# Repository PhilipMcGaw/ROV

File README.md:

# ROV

This is the software that runs my ROV (well an attempt at writing it anyway).\

uses RPi-Cam-Web-Interface

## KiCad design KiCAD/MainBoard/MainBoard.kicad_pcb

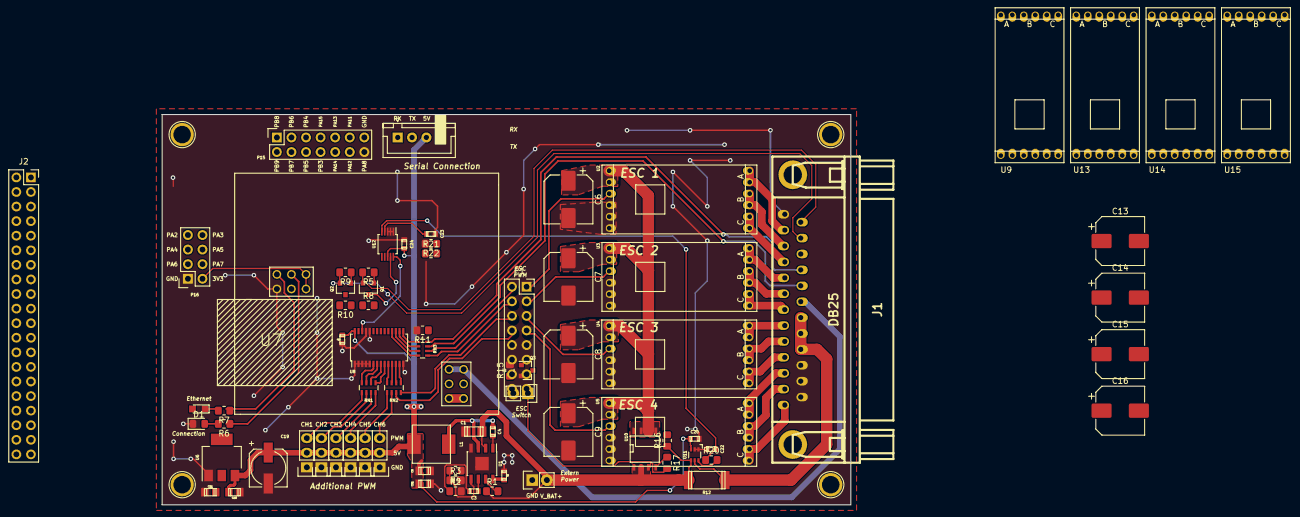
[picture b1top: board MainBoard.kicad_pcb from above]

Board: 2 copper layers, 120.0 x 68.0 mm, 82 parts (0 on the bottom side), 71 nets.

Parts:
C1: 10uF/25V; c_1206
C2, C20, C23, C24: 0.1uF; c_0603
C3: 3.9nF; c_0603
C4: 10nF; c_0603
C5, C21: 22uF/10V; c_0805
C6, C7, C8, C9, C13, C14, C15, C16: 220uF/25V; CP_Elec_8x10
C10, C11: 1uF; c_0805
C12: 10uF; c_0603
C19: 220uF/10V; CP_Elec_6.3x5.8
C22: 1uF; c_0603
D1: LED; LED_0805_2012Metric_Pad1.15x1.40mm_HandSolder
D2: LED; LED_0805
J1: DB25; DB_25M
J2: Raspberry_Pi_2_3; PinSocket_2x20_P2.54mm_Vertical
L1: 10uH/4A; ASPI-0630LR
P1: BDLC Enable; PinSocket_2x08_P2.54mm_Vertical
P2: CONN_01X04; JST_XH_B04B-XH-A_04x2.50mm_Straight
P4, P5, P6, P7: HOLE; 1pin
P8, P14: CONN_01X02; Socket_Strip_Straight_1x02
P9, P10, P11, P12, P13, P18: CONN_01X03; Socket_Strip_Straight_1x03
P15: CONN_02X07; Socket_Strip_Straight_2x07
P16: CONN_02X04; Socket_Strip_Straight_2x04
Q1, Q2: BSS138; SOT-23
Q3: DMN65D8L; SOT-23
R1: 100k; R_0805_2012Metric_Pad1.20x1.40mm_HandSolder
R2: 6.8k; R_0805_2012Metric_Pad1.20x1.40mm_HandSolder
R3, R22: 10k %1; R_0805_2012Metric_Pad1.20x1.40mm_HandSolder
R4: 44.2k 1%; R_0805_2012Metric_Pad1.20x1.40mm_HandSolder
R5, R8, R9, R10, R11, R15, R16: 10k; R_0805_2012Metric_Pad1.20x1.40mm_HandSolder
R6, R7: 330; R_0805_2012Metric_Pad1.20x1.40mm_HandSolder
R12: 0.003 %1; r_2512
R17: 1k; R_0805_2012Metric_Pad1.20x1.40mm_HandSolder
R20: 3.3k; R_0805_2012Metric_Pad1.20x1.40mm_HandSolder
R21: 30.1k 1%; R_0805_2012Metric_Pad1.20x1.40mm_HandSolder
RN1, RN2, RN3: 20k; R_Array_Concave_4x0603
U1: mp2307; SOIC-8-1EP_3.9x4.9mm_Pitch1.27mm
U2, U3, U4, U5, U9, U13, U14, U15: DYS_mini_ESC; DYS_Mini_ESC
U6: TLV1117LV33; SOT-223
U7: TENDA_P200; Tenda_p200
U8: pca9685; TSSOP-28_4.4x9.7mm_Pitch0.65mm
U10: SI4425DDY; SOIC-8-N
U11: INA199A2; SC-70-6
U12: ADS1015; MSOP-10_3x3mm_Pitch0.5mm

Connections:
+3V3: C11.1, D2.2 (A), J1.23, P16.2, Q1.1 (G), Q2.1 (G), R5.1, R9.1, U6.2 (VOUT), U6.4 (VOUT), U7.3V3
+5V: C5.1, C10.1, C12.1, C19.1, C20.1, C21.1, C24.1, J2.2 (5V), J2.4 (5V), L1.2, P2.3, P9.2, P10.2, P11.2, P12.2, P13.2, P18.2, R4.1, R8.1, R10.1, U6.3 (VIN), U8.28 (VDD), U11.3 (V+), U12.8 (VDD)
/ADC_I: C22.1, R20.1, U12.5 (AIN_1)
/ADC_V: C23.1, R21.2, R22.1, U12.4 (AIN_0)
/Brushless DC Controllers/ESC1: P1.1, U2.2 (PWM)
/Brushless DC Controllers/ESC2: P1.3, U3.2 (PWM)
/Brushless DC Controllers/ESC3: P1.5, U4.2 (PWM)
/Brushless DC Controllers/ESC4: P1.7, U5.2 (PWM)
/Brushless DC Controllers/ESC5: P1.9, U9.2 (PWM)
/Brushless DC Controllers/ESC6: P1.11, U13.2 (PWM)
/Brushless DC Controllers/ESC7: P1.13, U14.2 (PWM)
/Brushless DC Controllers/ESC8: P1.15, U15.2 (PWM)
/CH0: P9.3, RN1.1 (R1.1)
/CH1: P10.3, RN1.2 (R2.1)
/CH2: P11.3, RN1.3 (R3.1)
/CH3: P12.3, RN1.4 (R4.1)
/CH4: P13.3, RN2.1 (R1.1)
/CH5: P18.3, RN2.2 (R2.1)
/CH8: P1.2, RN3.8 (R1.2)
/CH9: P1.4, RN3.7 (R2.2)
/CH10: P1.6, RN3.6 (R3.2)
/CH11: P1.8, RN3.5 (R4.2)
/MOTOR_1A: J1.12, U2.4 (OUT_A)
/MOTOR_1B: J1.11, U2.5 (OUT_B)
/MOTOR_1C: J1.10, U2.6 (OUT_C)
/MOTOR_2A: J1.9, U3.4 (OUT_A)
/MOTOR_2B: J1.8, U3.5 (OUT_B)
/MOTOR_2C: J1.7, U3.6 (OUT_C)
/MOTOR_3A: J1.6, U4.4 (OUT_A)
/MOTOR_3B: J1.5, U4.5 (OUT_B)
/MOTOR_3C: J1.4, U4.6 (OUT_C)
/MOTOR_4A: J1.3, U5.4 (OUT_A)
/MOTOR_4B: J1.2, U5.5 (OUT_B)
/MOTOR_4C: J1.1, U5.6 (OUT_C)
/PWR_SW: Q3.1 (G), R15.1
/SCL_3V3: J1.24, J2.5 (SCL/GPIO3), Q2.2 (S), R9.2
/SCL_5V: Q2.3 (D), R10.2, U8.26 (SCL), U12.10 (SCL)
/SDA_3V3: J1.25, J2.3 (SDA/GPIO2), Q1.2 (S), R5.2
/SDA_5V: Q1.3 (D), R8.2, U8.27 (SDA), U12.9 (SDA)
/T+: J1.20, U7.T_+ (Tether+)
/V_BAT: C1.1, P8.2, R1.1, R12.1, R16.1, R21.1, U1.2 (IN), U10.1 (S), U10.2 (S), U10.3 (S), U11.4 (IN+)
/V_IN: J1.17, J1.18, J1.19, R12.2, U11.5 (IN-)
GND: C1.2, C2.2, C5.2, C6.2, C7.2, C8.2, C9.2, C10.2, C11.2, C12.2, C13.2, C14.2, C15.2, C16.2, C19.2, C20.2, C21.2, C22.2, C23.2, C24.2, D1.1 (K), J1.13, J1.14, J1.15, J1.16, J2.6 (GND), J2.9 (GND), J2.14 (GND), J2.20 (GND), J2.25 (GND), J2.30 (GND), J2.34 (GND), J2.39 (GND), P2.4, P8.1, P9.1, P10.1, P11.1, P12.1, P13.1, P14.2, P15.14, P16.1, P18.1, Q3.2 (S), R2.2, R3.2, R11.2, R15.2, R22.2, U1.4 (GND), U1.9 (GND), U2.1 (GND), U3.1 (GND), U4.1 (GND), U5.1 (GND), U6.1 (GND), U7.GND, U8.1 (A0), U8.2 (A1), U8.3 (A2), U8.4 (A3), U8.5 (A4), U8.14 (GND), U8.24 (A5), U8.25 (EXTCLK), U9.1 (GND), U11.1 (REF), U11.2 (GND), U12.1 (ADDR), U12.2 (ALERT), U12.3 (GND), U13.1 (GND), U14.1 (GND), U15.1 (GND)
unnamed: C3.2, R2.1
unnamed: D1.2 (A), R6.2
unnamed: D2.1 (K), R7.2
unnamed: P14.1, Q3.3 (D), R17.2
unnamed: RN1.8 (R1.2), U8.6 (PWM0)
unnamed: RN1.7 (R2.2), U8.7 (PWM1)
unnamed: RN1.6 (R3.2), U8.8 (PWM2)
unnamed: RN1.5 (R4.2), U8.9 (PWM3)
unnamed: RN2.8 (R1.2), U8.10 (PWM4)
unnamed: RN2.7 (R2.2), U8.11 (PWM5)
unnamed: RN2.6 (R3.2), U8.12 (PWM6)
unnamed: RN2.5 (R4.2), U8.13 (PWM7)
unnamed: RN3.1 (R1.1), U8.15 (PWM8)
unnamed: RN3.2 (R2.1), U8.16 (PWM9)
unnamed: RN3.3 (R3.1), U8.17 (PWM10)
unnamed: RN3.4 (R4.1), U8.18 (PWM11)
unnamed: C4.2, U1.1 (BS)
unnamed: C3.1, U1.6 (COMP)
unnamed: R1.2, U1.7 (EN)
unnamed: R3.1, R4.2, U1.5 (FB)
unnamed: C2.1, U1.8 (SS)
unnamed: C4.1, L1.1, U1.3 (SW)
unnamed: R6.1, U7.C (Connection_LED)
unnamed: R7.1, U7.E (Ethernet_LED)
unnamed: R11.1, U8.23 (~OE)
unnamed: R16.2, R17.1, U10.4 (G)
unnamed: R20.2, U11.6 (OUT)
V_PWR: C6.1, C7.1, C8.1, C9.1, C13.1, C14.1, C15.1, C16.1, U2.3 (VCC), U3.3 (VCC), U4.3 (VCC), U5.3 (VCC), U9.3 (VCC), U10.5 (D), U10.6 (D), U10.7 (D), U10.8 (D), U13.3 (VCC), U14.3 (VCC), U15.3 (VCC)

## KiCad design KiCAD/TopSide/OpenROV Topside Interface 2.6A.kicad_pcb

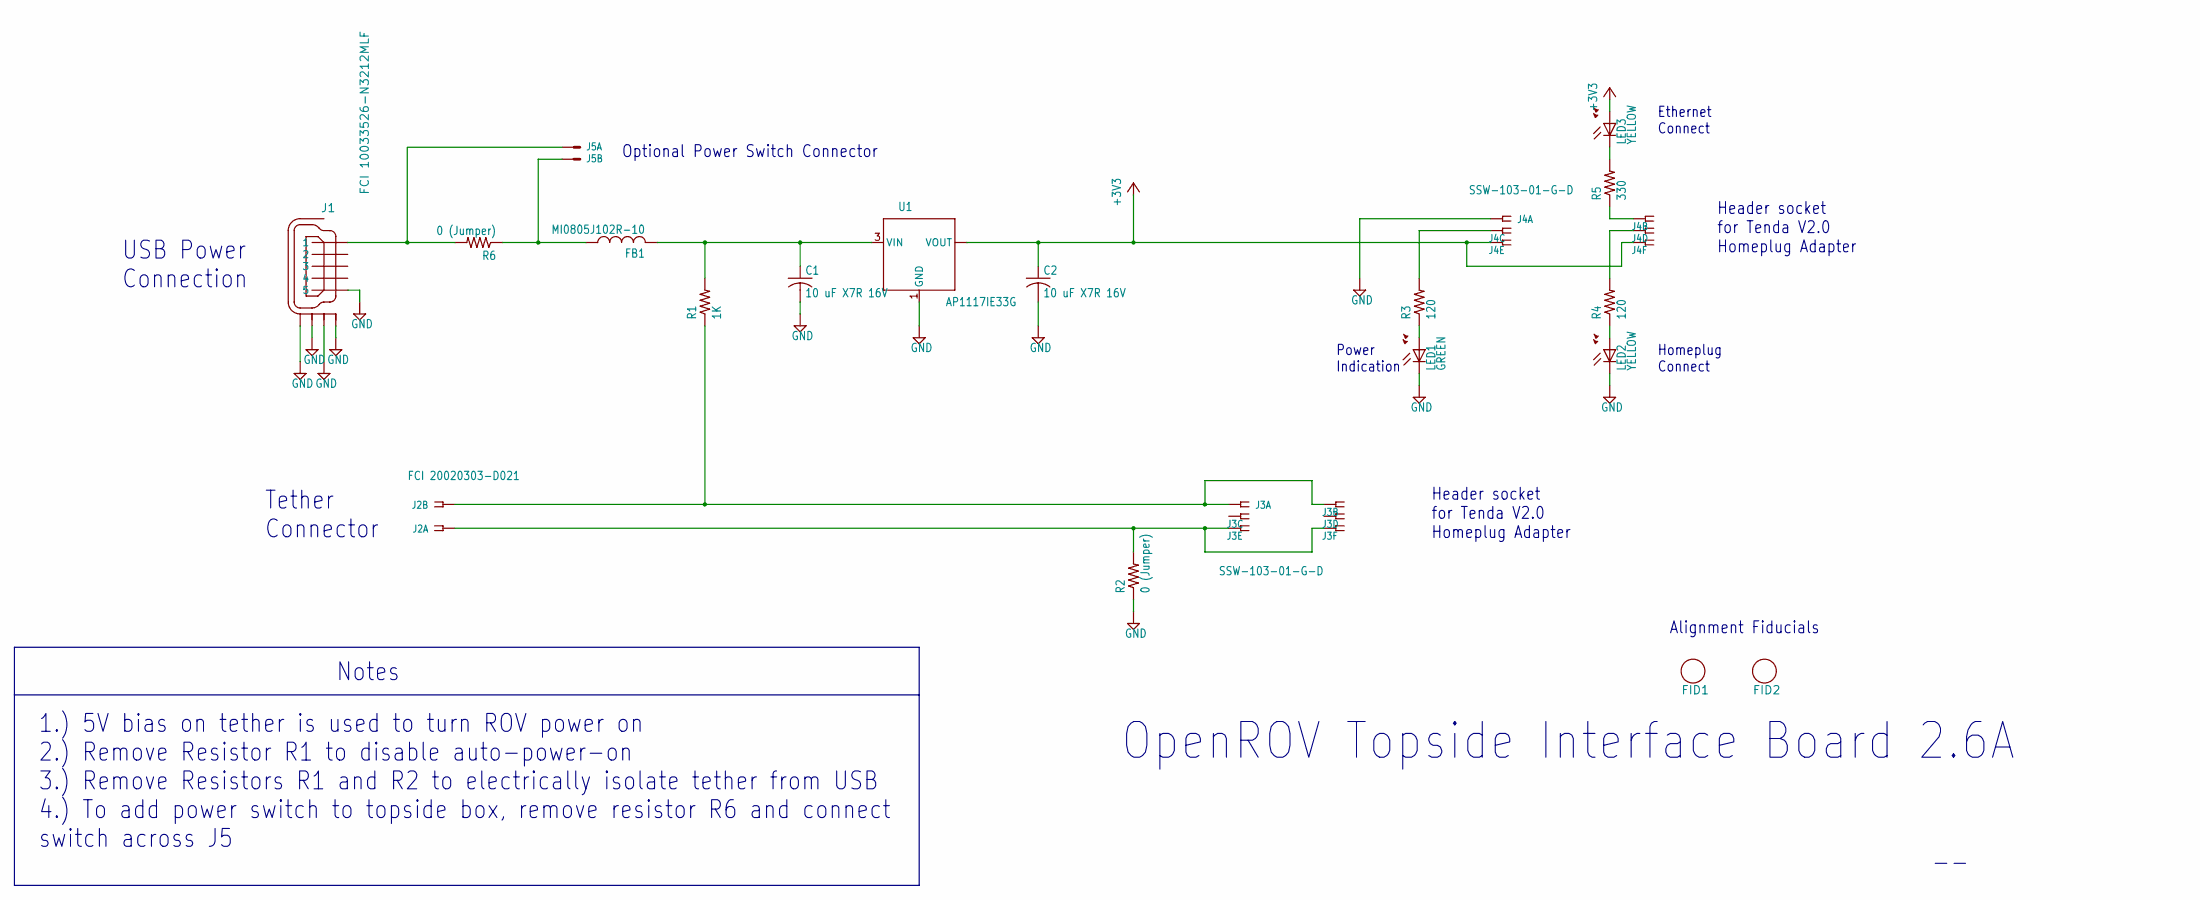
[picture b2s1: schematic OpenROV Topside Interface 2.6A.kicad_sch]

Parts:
C1, C2: 10 uF X7R 16V; R1206
FB1: MI0805J102R-10; R0805
FID1, FID2: FIDUCIAL_1
J1: FCI 10033526-N3212MLF; USB_MINI-B_SM
J2: FCI 20020303-D021; FCI_09-381_2PL
J3, J4: SSW-103-01-G-D; SSW-103-02-S-D
J5: HDR_1X2X0.100-ALT_SILK; 22-23-2021_ALT_SILK
LED1: GREEN; LED_0805_BOTTOM_MT(OSRAM)
LED2, LED3: YELLOW; LED_0805_BOTTOM_MT(OSRAM)
R1: 1K; R0805
R2, R6: 0 (Jumper); R0805
R3, R4: 120; R0805
R5: 330; R0805
U1: AP1117IE33G; SOT223

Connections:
+3V3: C2.1, J4.5, J4.6, LED3.A, U1.2 (VOUT), U1.4 (VOUT)
GND: C1.2, C2.2, J1.5, J1.M1 (S1), J1.M2 (S2), J1.M3 (S3), J1.M4 (S4), J4.1, LED1.C, LED2.C, R2.1, U1.1 (GND)
unnamed: J2.1A, J2.1B, J3.5, J3.6, R2.2
unnamed: J2.2A, J2.2B, J3.1, J3.2, R1.1
unnamed: J1.1, J5.1, R6.2
unnamed: C1.1, FB1.2, R1.2, U1.3 (VIN)
unnamed: LED3.C, R5.2
unnamed: J4.3, R3.2
unnamed: LED1.A, R3.1
unnamed: LED2.A, R4.1
unnamed: J4.4, R4.2
unnamed: FB1.1, J5.2, R6.1
unnamed: J4.2, R5.1

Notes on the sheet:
1.) 5V bias on tether is used to turn ROV power on 2.) Remove Resistor R1 to disable auto-power-on 3.) Remove Resistors R1 and R2 to electrically isolate tether from USB 4.) To add power switch to topside box, remove resistor R6 and connect switch across J5
Alignment Fiducials
Homeplug Connect
USB Power Connection
Power Indication
Optional Power Switch Connector
Header socket for Tenda V2.0 Homeplug Adapter
Notes
OpenROV Topside Interface Board 2.6A
Tether Connector
Ethernet Connect

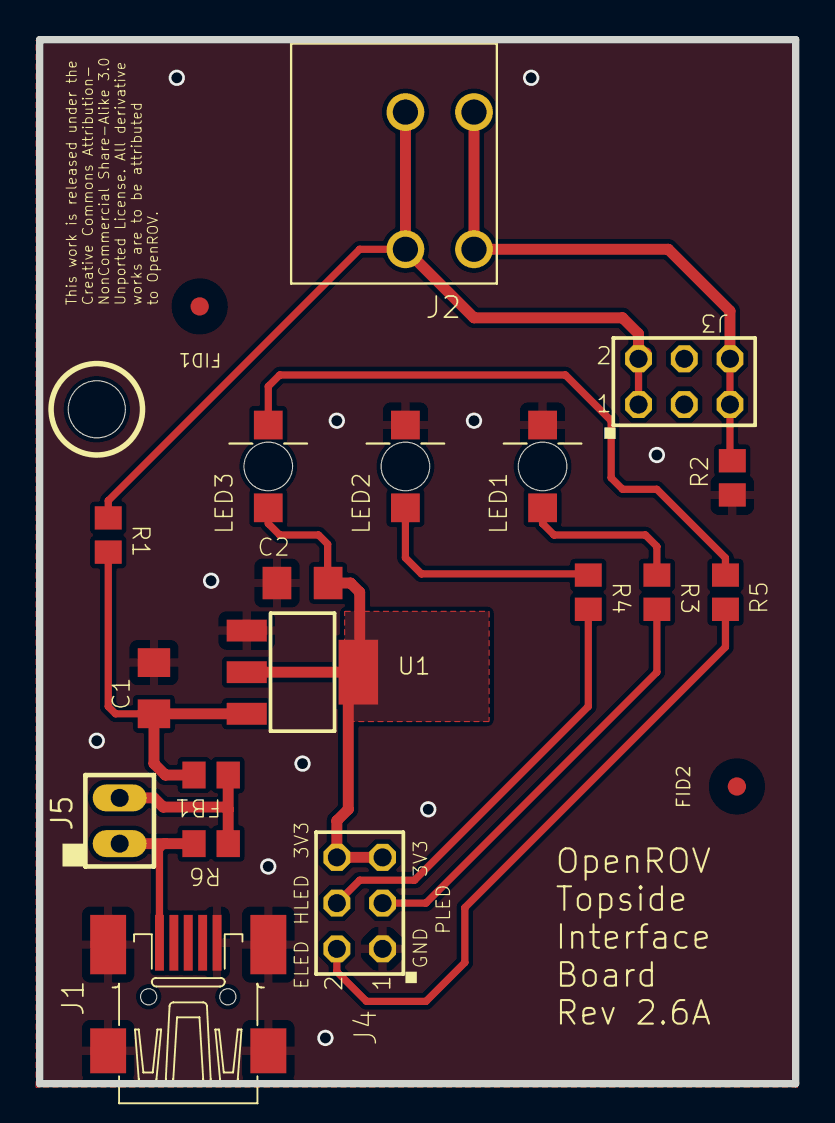
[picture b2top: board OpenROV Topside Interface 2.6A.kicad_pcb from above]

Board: 4 copper layers, 42.0 x 58.0 mm, 21 parts (0 on the bottom side), 13 nets.

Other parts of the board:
UNK_HOLE_0: dummyfp0

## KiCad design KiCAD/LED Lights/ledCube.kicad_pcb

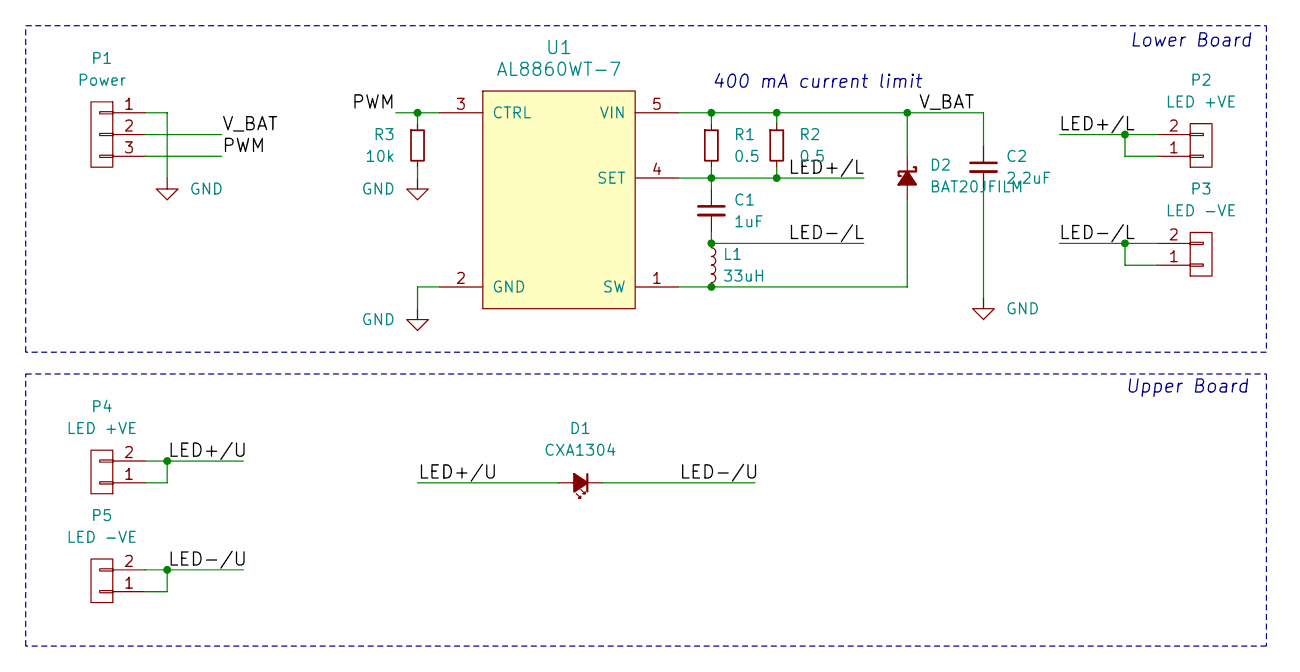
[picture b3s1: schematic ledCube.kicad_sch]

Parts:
C1: 1uF; C_0805_2012Metric_Pad1.18x1.45mm_HandSolder
C2: 2.2uF; C_0805_2012Metric_Pad1.18x1.45mm_HandSolder
D1: CXA1304; Part # CXA1304-0000-000N00B440F-ND; Farnell 3430040
D2: BAT20JFILM; SOD-323_HandSoldering; Part # 497-3381-1-ND
L1: 33uH; inductor_33uH; Part # SRN6045-330MCT-ND
P1: Power; Socket_Strip_Straight_1x03
P2, P4: LED +VE; Socket_Strip_Straight_1x02
P3, P5: LED -VE; Socket_Strip_Straight_1x02
R1, R2: 0.5; R_1206_3216Metric_Pad1.30x1.75mm_HandSolder; Part # 311-0.5LWCT-ND
R3: 10k; R_0805_2012Metric_Pad1.20x1.40mm_HandSolder
U1: AL8860WT-7; SOT-23-5; Part # AL8860WT-7DICT-ND

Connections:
/LED+/L: C1.1, P2.1, P2.2, R1.2, R2.2, U1.4 (SET)
/LED+/U: D1.2 (A), P4.1, P4.2
/LED-/L: C1.2, L1.1, P3.1, P3.2
/LED-/U: D1.1 (K), P5.1, P5.2
/PWM: P1.3, R3.1, U1.3 (CTRL)
/V_BAT: C2.1, D2.1 (K), P1.2, R1.1, R2.1, U1.5 (VIN)
GND: C2.2, P1.1, R3.2, U1.2 (GND)
unnamed: D2.2 (A), L1.2, U1.1 (SW)

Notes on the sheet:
Upper Board
Lower Board
400 mA current limit

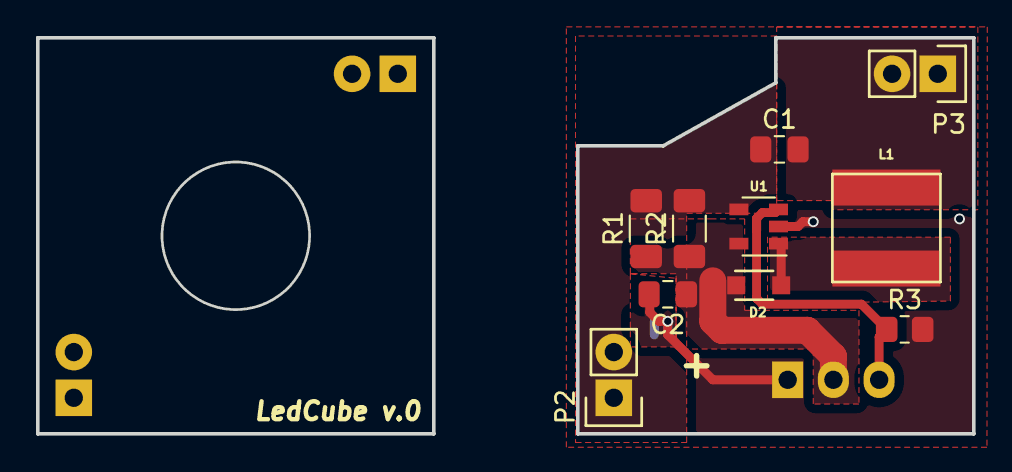
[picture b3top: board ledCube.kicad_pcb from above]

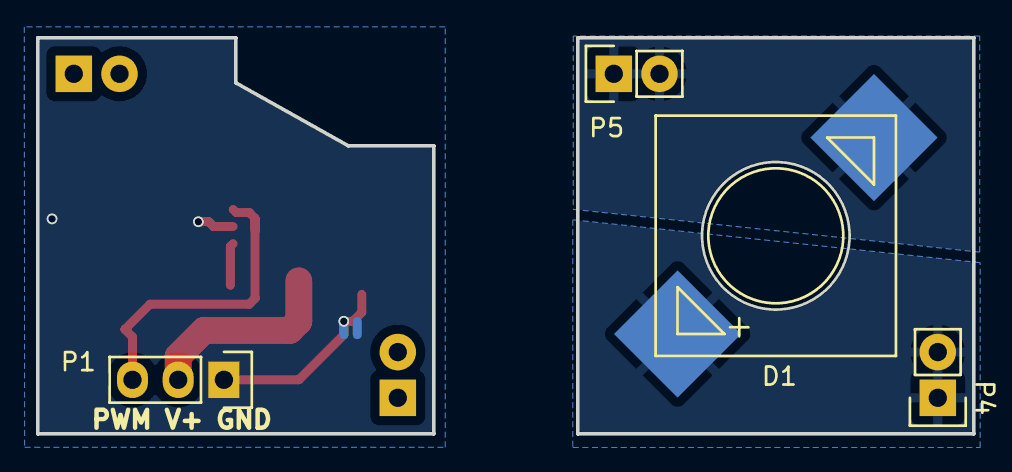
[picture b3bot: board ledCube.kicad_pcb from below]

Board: 2 copper layers, 52.0 x 22.0 mm, 14 parts (4 on the bottom side), 8 nets.

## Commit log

2021-12-20 initial
2021-12-20 track
2021-12-20 cleanup
2021-12-28 Made some changes
2021-12-28 Authorized keys added
2023-07-02 removed absolute reference to resources
2023-07-02 removed referential links
2023-07-02 added some details
2023-07-02 fixed battery levels
2023-07-02 updated the front page to make pretty
    added more snaz
2023-07-02 battery icon
2023-07-03 using fontawsome / bootstrap colours on the battery logo rather than static stylescript
2023-07-03 Attempting to use RPi-Cam-Web-Interface as a base for a better interface
2023-07-04 Thanks to Ross for suggestion
2023-07-04 ¿upgrade? to bootstrap three?
2023-07-04 Added un-minified bootstrap 3.5
2023-07-15 Added draw.io file
2023-07-30 some changes
2025-08-13 updated LED Cube to latest kicad
2025-08-13 clean up the home plug and other things not on grid
2025-08-13 BLDC controller clean up
2025-08-13 remove pre KiCAD 9 files
    remove old files
2025-08-13 clean up
2025-08-13 400 mA limit spelling fix
2025-08-13 removed gerber folder
2025-08-13 Fixed Vendor spelling
2025-08-13 removal of vias
2025-08-13 tried to make updated path
2025-08-15 git ignore del
2025-08-18 remove old files
2025-08-18 update pcb
2025-08-18 moved BLDC to seperate sheet
2025-08-18 3D model for the LED
2025-08-19 resources
2025-08-20 Added the OpenROV topside interface and converted to KiCAD
2025-08-20 change
2025-08-21 libery change
2025-08-22 change pins

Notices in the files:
KiCAD/TopSide/OpenROV Topside Interface 2.6A.kicad_pcb:
This work is released under the
Creative Commons Attribution-
